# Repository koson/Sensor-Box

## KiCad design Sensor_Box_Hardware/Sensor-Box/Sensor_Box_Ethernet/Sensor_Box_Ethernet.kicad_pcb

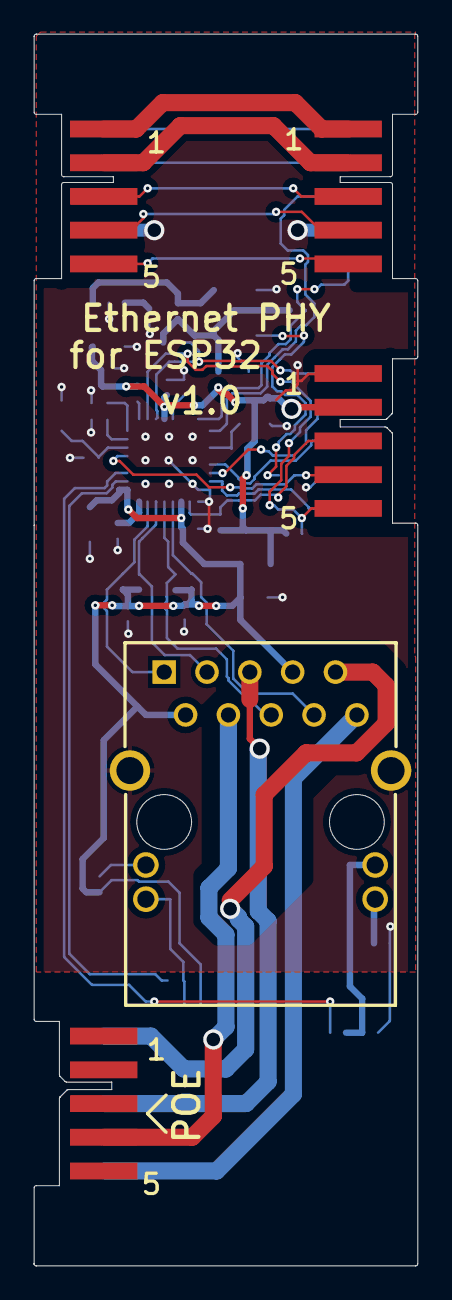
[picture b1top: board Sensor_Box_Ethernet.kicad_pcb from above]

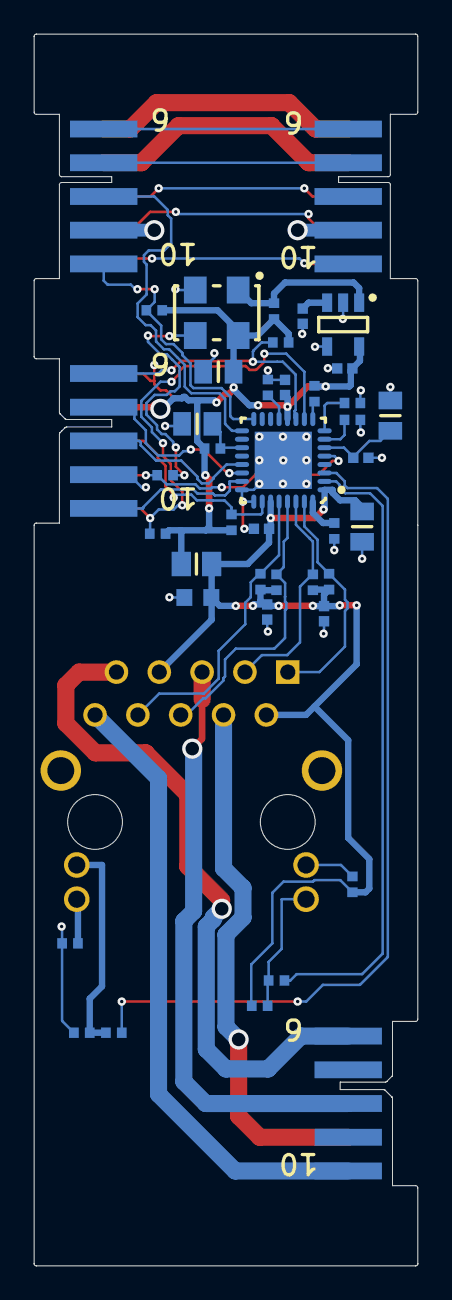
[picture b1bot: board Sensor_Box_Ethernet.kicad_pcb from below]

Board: 2 copper layers, 22.8 x 73.1 mm, 45 parts (38 on the bottom side), 43 nets.

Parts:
C17, C18: 10uF; _Dropbox_DESIGNS_COMMON_LIBS_CernLib_2017_12_02_Capacitors.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
C19, C20: 100nF; _Dropbox_DESIGNS_COMMON_LIBS_CernLib_2017_12_19_Capacitors.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
C21, C23, C26: 100nF; _Dropbox_DESIGNS_COMMON_LIBS_CernLib_2018_3_3_PcbLib_Capaci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
C22: 10nF; _Dropbox_DESIGNS_COMMON_LIBS_CernLib_2017_12_02_PcbLib_Capa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
C24, C25: 10uF; _Dropbox_DESIGNS_COMMON_LIBS_CernLib_2018_3_3_PcbLib_Capaci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
C27, C28: 100nF; _Dropbox_DESIGNS_COMMON_LIBS_CernLib_2017_12_19_PcbLib_Capa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
FB1: 220R@100MHz; _Dropbox_DESIGNS_COMMON_LIBS_CernLib_2017_12_02_PcbLib_Indu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
IC6: LAN8710A-EZC; _Dropbox_DESIGNS_COMMON_LIBS_CernLib_2018_3_3_PcbLib_ICs An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
IC7: BD5230FVE-TR; SOT95P280X145-5N
J2, J7, J10, J11: =Family; _Dropbox_DESIGNS_COMMON_LIBS_CernLib_2018_3_3_PcbLib_Miscel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
J8, J9: =Family; _Dropbox_DESIGNS_COMMON_LIBS_CernLib_2018_3_3_Connectors.Db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
J93: RJ45; ABRACON_ARJM11C7-114-BA-EW2
OSC1: 50MHz; _Dropbox_DESIGNS_COMMON_LIBS_CernLib_2017_12_19_PcbLib_ICs 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
R10, R27, R29, R30, R31, R32, R34, R35, R38: 10k; _Dropbox_DESIGNS_COMMON_LIBS_CernLib_2018_3_3_PcbLib_Resist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
R11, R24: 330; _Dropbox_DESIGNS_COMMON_LIBS_CernLib_2018_3_3_PcbLib_Resist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
R25, R26: 49R9; _Dropbox_DESIGNS_COMMON_LIBS_CernLib_2017_12_02_PcbLib_Resi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
R28, R33: 49R9; _Dropbox_DESIGNS_COMMON_LIBS_CernLib_2018_3_3_PcbLib_Resist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
R36: 10k; _Dropbox_DESIGNS_COMMON_LIBS_CernLib_2017_12_02_Resistors.D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
R37, R41: 10k; _Dropbox_DESIGNS_COMMON_LIBS_CernLib_2017_12_19_PcbLib_Resi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
R39: 12k1; _Dropbox_DESIGNS_COMMON_LIBS_CernLib_2018_3_3_PcbLib_Resist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
R40: 10; _Dropbox_DESIGNS_COMMON_LIBS_CernLib_2017_12_19_PcbLib_Resi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
R85, R86: 330; _Dropbox_DESIGNS_COMMON_LIBS_CernLib_2018_03_29_PcbLib_Resi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

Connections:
AVDDT_PHY: C18.1, C19.2, C20.2, C21.1, C22.2, FB1.1, IC6.1, IC6.27, J93.4, J93.9, R25.1, R26.1, R28.2, R33.2, R36.2, R85.1
CLK: IC6.5, J11.4, R40.2
GND: C17.2, C18.2, C19.1, C20.1, C21.2, C22.1, C23.1, C24.1, C25.2, C26.1, C27.1, C28.1, IC6.24, IC6.25, IC6.33, IC7.2, IC7.4, J7.9, J8.9, J11.1, J11.9, J93.S1, J93.S2, OSC1.2, R27.2, R32.2, R34.2, R37.2, R39.1, R86.1
GSM_PWR: J7.7, J8.7
LED1: J93.L3, R11.2, R37.1
LED2: J93.L2, R24.2, R36.1
MDC: IC6.17, J8.8
MDIO: IC6.16, J8.10, R10.1
NetC24_2: C24.2, IC6.19, R38.1
NetC27_2: C27.2, IC7.3
NetIC6_2: IC6.2, R24.1
NetIC6_3: IC6.3, R11.1
NetIC6_7: IC6.7, R32.1
NetIC6_8: IC6.8, R34.1
NetIC6_9: IC6.9, R35.1
NetIC6_13: IC6.13, R27.1
NetIC6_32: IC6.32, R39.2
NetJ93_L1: J93.L1, R85.2
NetJ93_L4: J93.L4, R86.2
NetOSC1_3: OSC1.3, R40.1
OSC_DIS: IC7.1, OSC1.1, R41.2
P3V3: C17.1, C23.2, C28.2, FB1.2, IC6.12, IC7.5, J11.2, OSC1.4, R10.2, R29.2, R30.2, R31.2, R35.2, R38.2, R41.1
P5V0: J7.1, J8.1
P12V0: J7.2, J8.2
PHY_RD_N: IC6.28, J93.3, R26.2
PHY_RD_P: IC6.29, J93.5, R25.2
PHY_TD_N: IC6.30, J93.8, R33.1
PHY_TD_P: IC6.31, J93.10, R28.1
POE_VC1: J10.4, J93.7
POE_VC2: J10.6, J93.2
POE_VC3: J10.8, J93.6
POE_VC4: J10.10, J93.1
RXD0: IC6.11, J11.6, R29.1
RXD1: IC6.10, J11.5, R30.1
RX_DV: IC6.26, J11.3, R31.1
TXD0: IC6.22, J11.7
TXD1: IC6.23, J11.10
TX_EN: IC6.21, J11.8
U1_CTS: J7.6, J8.6
U1_RTS: J7.4, J8.4
U1_RXD: J7.3, J8.3
U1_TXD: J7.5, J8.5
VDCR: C25.1, C26.2, IC6.6

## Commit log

2023-01-23 convert to Kicad
